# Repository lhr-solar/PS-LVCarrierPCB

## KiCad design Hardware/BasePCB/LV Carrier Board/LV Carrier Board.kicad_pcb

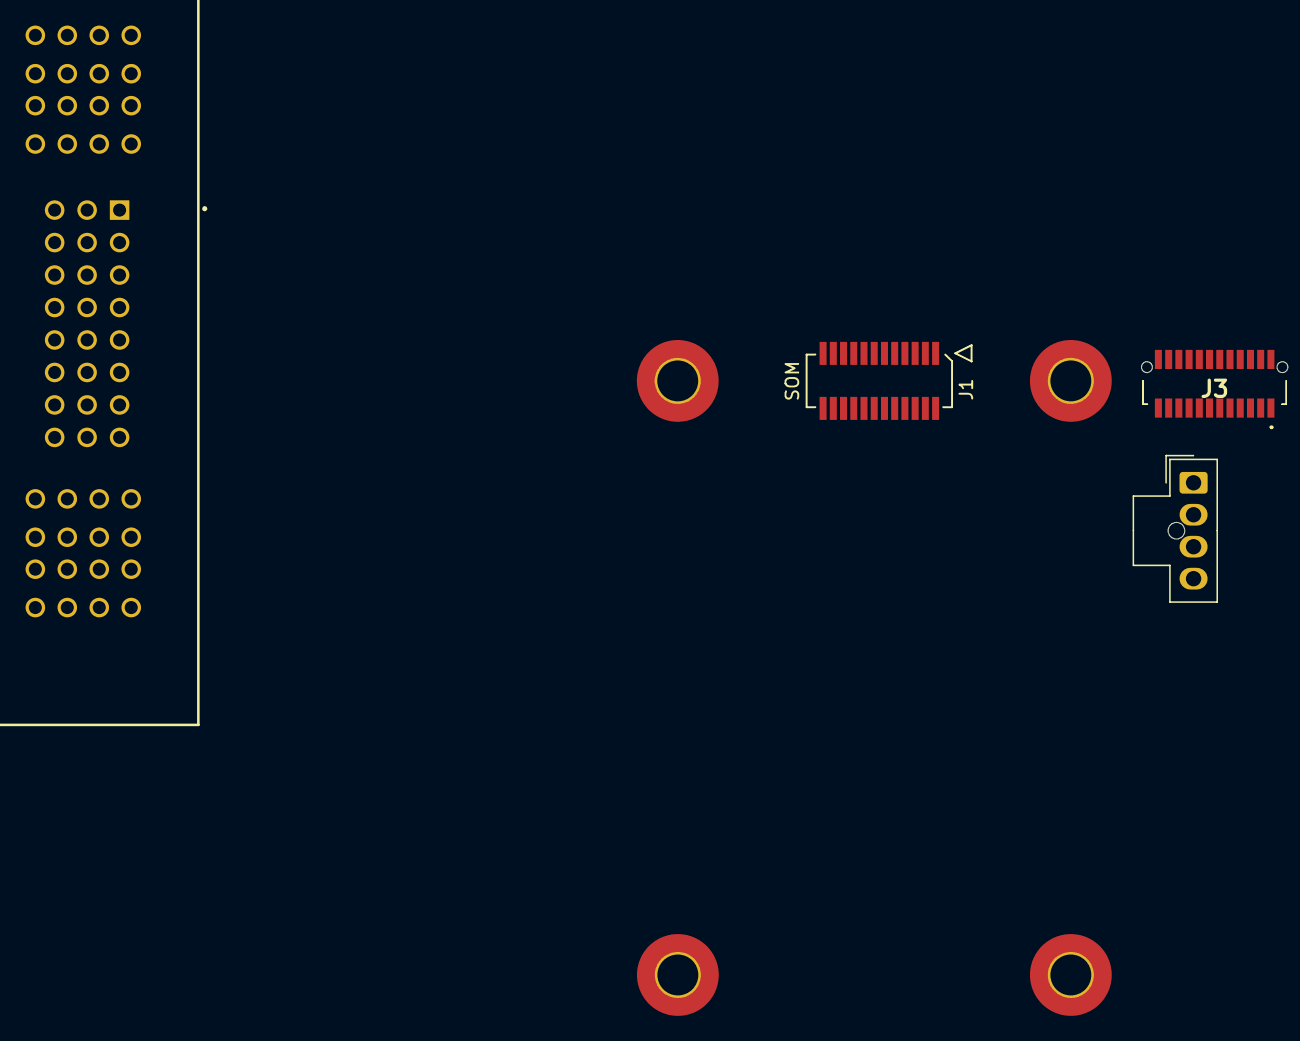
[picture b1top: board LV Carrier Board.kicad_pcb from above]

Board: 2 copper layers, 4 parts (0 on the bottom side), 5 nets, no tracks yet.

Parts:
J1: 53307-2471; PeripheralSOM
J3: 52465-2470; 524652470
J4: PeripheralCAN; Molex_Nano-Fit_105309-xx04_1x04_P2.50mm_Vertical
U4: Maxi_Carrier_Connector

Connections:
/24Out: J3.19, U4.P03 (OUT+)
GND: J1.1 (GND), J1.3 (GND), J1.5 (GND), J4.2 (GND)
unnamed: J1.24 (+24V_In), J4.1 (24V)
unnamed: J1.22 (CAN_H), J4.3 (CAN_H)
unnamed: J1.20 (CAN_L), J4.4 (CAN_L)

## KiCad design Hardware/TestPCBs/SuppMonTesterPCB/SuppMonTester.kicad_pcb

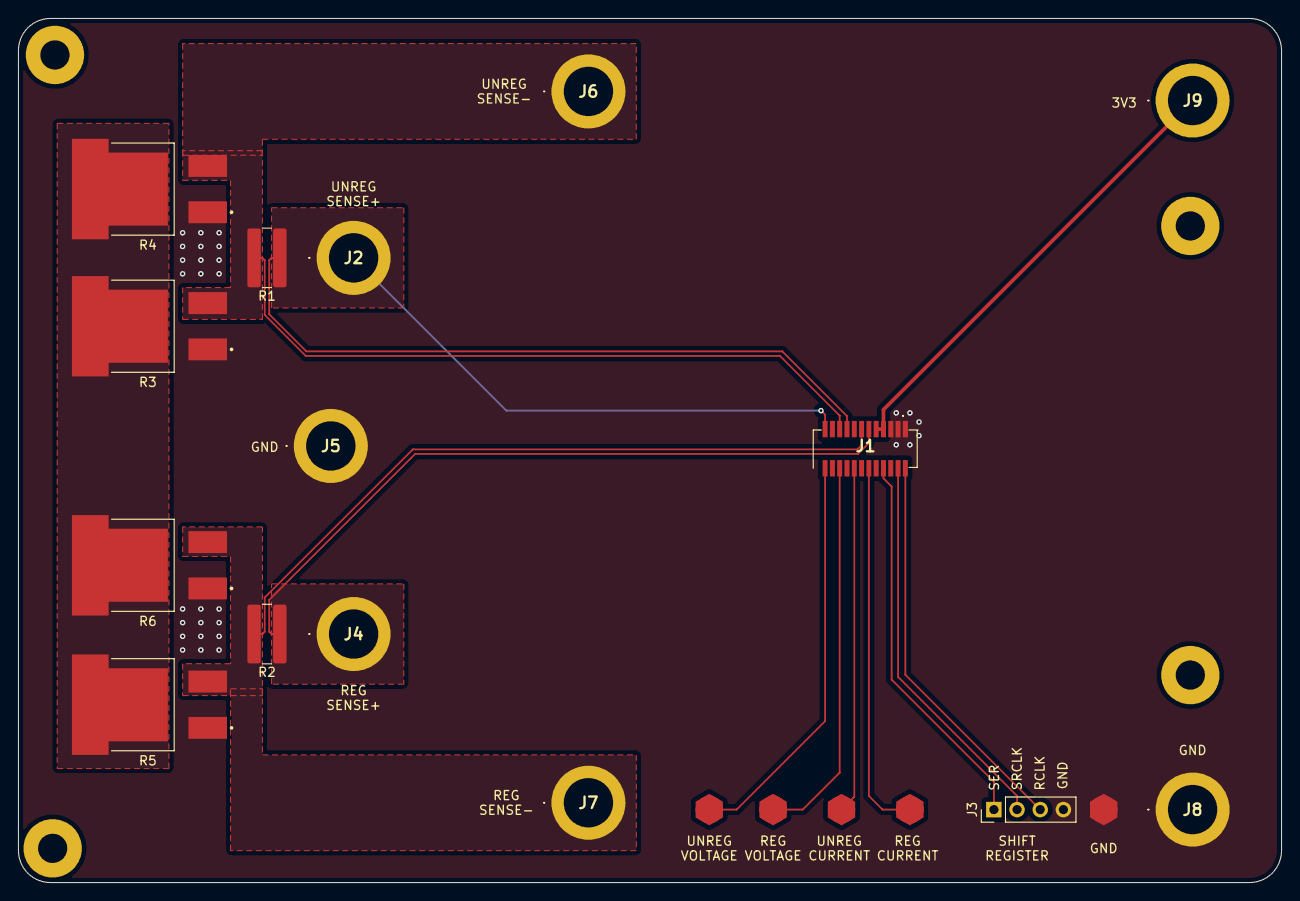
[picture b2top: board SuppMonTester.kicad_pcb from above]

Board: 2 copper layers, 138.5 x 94.8 mm, 24 parts (0 on the bottom side), 14 nets.

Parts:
H1, H2, H3, H4: MountingHole_Pad_MP; MountingHole_3.2mm_M3_Pad
J1: 53307-2471; 533072471
J2: UNREG+; 5754
J3: SHIFT_REG; PinHeader_1x04_P2.54mm_Vertical
J4: REG+; 5754
J5, J8: GND; 5754
J6: UNREG-; 5754
J7: REG-; 5754
J9: 3V3; 5754
R1, R2: 250u; R_1225_3264Metric_Pad1.47x6.45mm_HandSolder
R3, R4, R5, R6: 20; RES_PWR263S-35-3300F
TP1: UNREG_VOLTAGE; TestPoint_HEX_3mmID
TP2: REG_VOLTAGE; TestPoint_HEX_3mmID
TP3: UNREG_CURRENT; TestPoint_HEX_3mmID
TP4: REG_CURRENT; TestPoint_HEX_3mmID
TP5: GND; TestPoint_HEX_3mmID

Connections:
+3.3V: J1.7, J1.9, J9.1
/RCLK: J1.2, J3.3
/REG_CURRENT: J1.12, TP4.1
/REG_SENSE+: J1.11, J4.1, R2.1
/REG_SENSE-: J1.13, J7.1, R2.2, R5.2, R6.2
/REG_VOLTAGE: J1.20, TP2.1
/SER: J1.8, J3.1
/SRCLK: J1.4, J3.2
/THERMAL_PAD: R3.3, R4.3, R5.3, R6.3
/UNREG_CURRENT: J1.16, TP3.1
/UNREG_SENSE+: J1.17, J1.23, J2.1, R1.1
/UNREG_SENSE-: J1.19, J6.1, R1.2, R3.2, R4.2
/UNREG_VOLTAGE: J1.24, TP1.1
GND: J1.1, J1.3, J1.5, J3.4, J5.1, J8.1, R3.1, R4.1, R5.1, R6.1, TP5.1
